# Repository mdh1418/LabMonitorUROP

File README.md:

# LabMonitor

UROP with Prof. Joe Steinmeyer to bring out a low cost and small footprint system to monitor environmental data within a laboratory setting.

## Getting Started

For this project, we are using the ESP32 (https://www.espressif.com/en/products/hardware/esp32/overview), the BME680 environmental sensor (https://cdn-shop.adafruit.com/product-files/3660/BME680.pdf), as well as a customized PCB for a minimal barebones setup. The ESP32 and BME680 are interfaced using I2C.

### Setup (WITHOUT PCB)

Materials
* ESP32-DevKitC (https://www.espressif.com/en/products/hardware/esp32-devkitc/overview)
* Adafruit BME680 (https://learn.adafruit.com/adafruit-bme680-humidity-temperature-barometic-pressure-voc-gas)
* Jumper cables
* USB to MicroUSB cable
* Breadboard

After installing the software listed below in the Software section to program the ESP32-DevKitC with Arduino, simply follow the hookup guide outlined in the Adafruit tutorial linked above in the materials list.

Materials
* ESP-Wroom-32 (https://www.espressif.com/en/products/hardware/esp-wroom-32/overview)
* BME680 (https://www.bosch-sensortec.com/bst/products/all_products/bme680)
* Sparkfun FTDI (https://www.sparkfun.com/products/9716)
* Customized PCB
* 2 Buttons (Reset and Prgm)
* Wires
* Breadboard

After installing the software listed below in the Software section to program the ESP-Wroom-32, (

Notes
* Use 3.3V on the FTDI so cut the 5V connection and solder the 3.3V connection
* To program the ESP-Wroom-32, press Reset, press Prgm, release Reset, and release Prgm and upload the sketch
* When using wifi, the FTDI driver cannot supply enough current, so power using batteries or a lab supply

### Software

Programming the ESP32 with Arduino
https://github.com/espressif/arduino-esp32

BME680 Driver
https://github.com/BoschSensortec/BME680_driver

KiCad (If customizing PCB)
http://kicad.org/

### References
http://esp32.net/
https://www.espressif.com/sites/default/files/documentation/esp32_hardware_design_guidelines_en.pdf
https://www.espressif.com/sites/default/files/documentation/esp-wroom-32_datasheet_en.pdf
https://3.bp.blogspot.com/-zyGHuqISKPs/WMx4MWPAZOI/AAAAAAAAAMw/xxDcpwVSq0garkCG5n8yQfn4X7r94zMHACLcB/s1600/ESP%2B32%2BSchematic.PNG
https://cdn-shop.adafruit.com/product-files/3660/BME680.pdf
https://learn.adafruit.com/adafruit-bme680-humidity-temperature-barometic-pressure-voc-gas/arduino-wiring-test
https://www.14core.com/wiring-and-flashing-programming-esp-32-esp32s-with-usb-ttl-uart/
https://github.com/sparkfun/SparkFun-KiCad-Libraries
https://www.wayneandlayne.com/blog/2013/02/27/kicad-tutorial-gerber-file-generation/
https://techtutorialsx.com/2017/04/24/esp32-publishing-messages-to-mqtt-topic/

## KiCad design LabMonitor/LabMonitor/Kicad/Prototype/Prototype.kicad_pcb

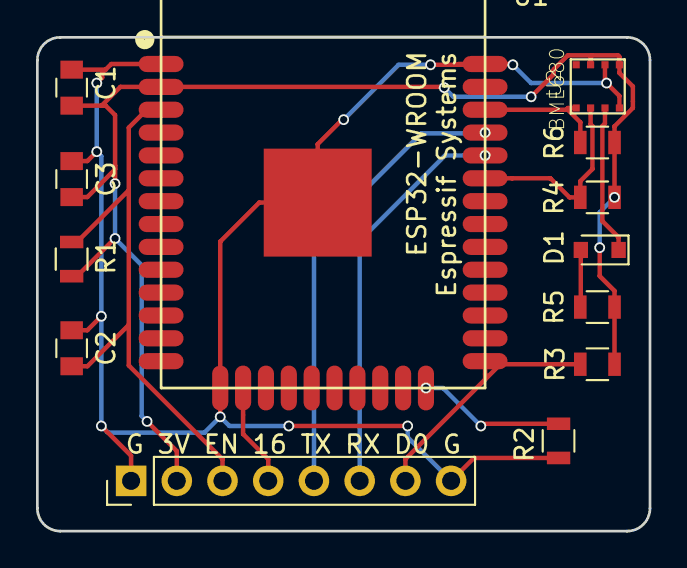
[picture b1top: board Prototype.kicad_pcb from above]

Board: 2 copper layers, 34.0 x 27.4 mm, 13 parts (0 on the bottom side), 12 nets.

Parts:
C1: 100uF/6.3V(20%); C_0805
C2: 1nF/50V(10%); C_0805
C3: 1uF/10V(10%); C_0805
D1: 1N4148; D_0805
G 3V EN 16 TX RX D0 G: Conn_01x08; Socket_Strip_Straight_1x08_Pitch2.54mm
R1: 12K(1%); R_0805
R2, R3: 5K(1%)(NC); R_0805
R4, R5, R6: 10K; R_0805
U1: ESP32-WROOM
U2: BME680

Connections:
16: G 3V EN 16 TX RX D0 G.4, U1.16
+3V3: C1.1, C3.1, G 3V EN 16 TX RX D0 G.2, R1.1, R3.1, R4.1, R5.1, R6.1, U1.2, U2.6, U2.8
CSB: D1.1, U2.2
D0: G 3V EN 16 TX RX D0 G.7, R3.2, U1.25
EN: C2.1, G 3V EN 16 TX RX D0 G.3, R1.2, U1.3
GND: C1.2, C2.2, C3.2, G 3V EN 16 TX RX D0 G.1, G 3V EN 16 TX RX D0 G.8, R2.1, U1.1, U1.15, U1.38, U1.39, U2.1, U2.7
unnamed: D1.2, R5.2
unnamed: R2.2, U1.24
RX: G 3V EN 16 TX RX D0 G.6, U1.34
SCK: R6.2, U1.36, U2.4
SDI: R4.2, U1.33, U2.3
TX: G 3V EN 16 TX RX D0 G.5, U1.35

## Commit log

2018-03-18 Added all relevant files
2018-03-18 added kicad and bme-micropython
2018-03-27 Updated README.md
    Began getting started section
2018-04-01 Testing image wiki upload
2018-10-26 Add README.md
2021-11-08 Update README.md
    https://forum.kicad.info/t/warning-avoid-all-links-to-kicad-pcb-org-use-kicad-org/31521
